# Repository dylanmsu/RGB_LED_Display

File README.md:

# RGB Led Display

## Board
| Front | Back |
|---|---|
| |  |

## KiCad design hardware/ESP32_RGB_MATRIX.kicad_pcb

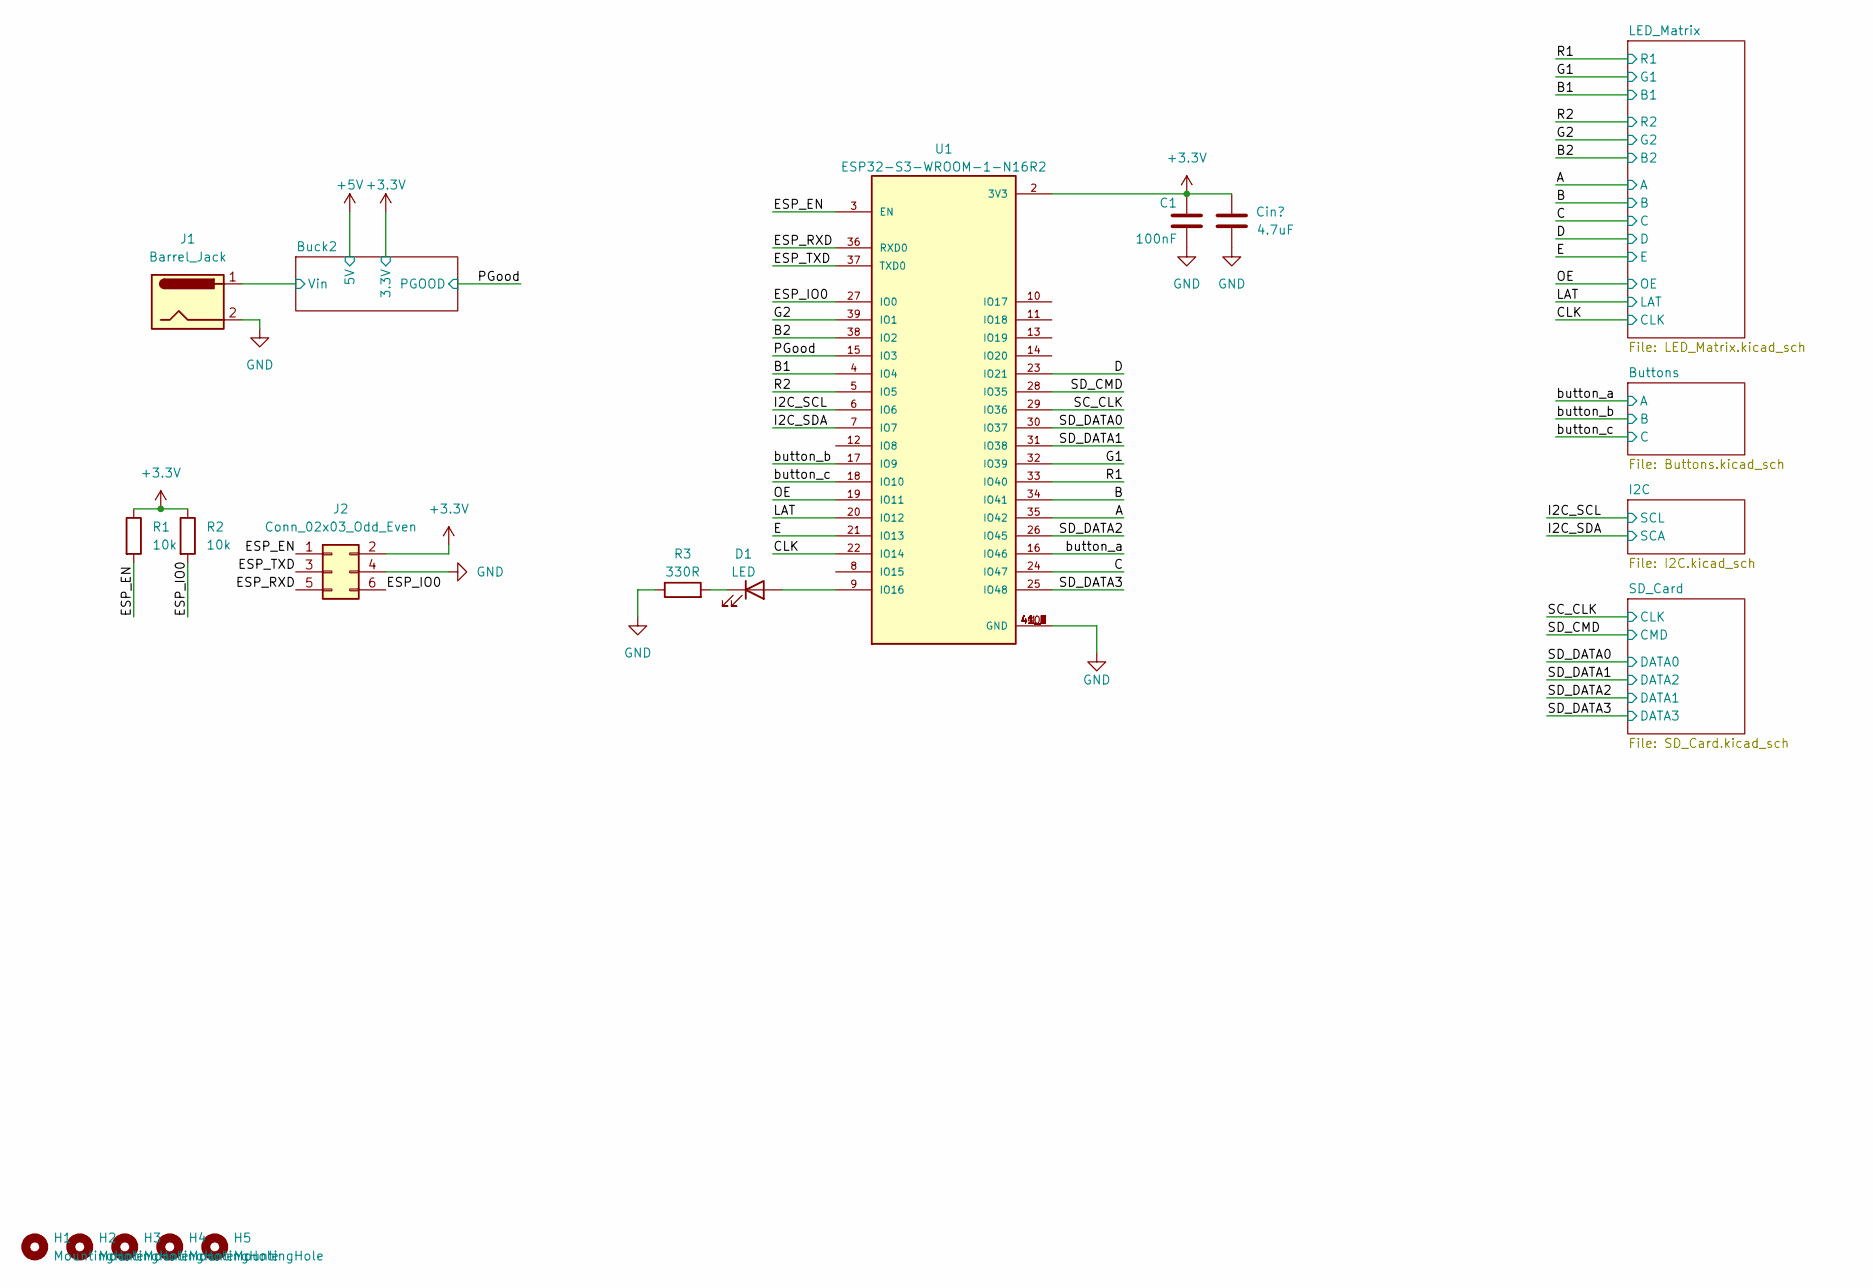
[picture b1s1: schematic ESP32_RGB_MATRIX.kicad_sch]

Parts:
C1: 100nF; C_0603_1608Metric
C2: 4.7uF; C_0805_2012Metric
D1: LED; LED_0805_2012Metric
H1, H2, H3, H4, H5: MountingHole; MountingHole_3.2mm_M3_DIN965_Pad
J1: Barrel_Jack; BarrelJack_Wuerth_6941xx301002
J2: Conn_02x03_Odd_Even; IDC-Header_2x03_P2.54mm_Vertical
R1, R2: 10k; R_0603_1608Metric
R3: 330R; R_0603_1608Metric
U1: ESP32-S3-WROOM-1-N16R2; XCVR_ESP32-S3-WROOM-1-N16R2; PARTREV v1.0

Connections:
+3.3V: C1.1, C2.1, J2.2, R1.1, R2.1, U1.2 (3V3); also elsewhere on the board
/A: U1.35 (IO42); also elsewhere on the board
/B: U1.34 (IO41); also elsewhere on the board
/B1: U1.4 (IO4); also elsewhere on the board
/B2: U1.38 (IO2); also elsewhere on the board
/Buck2/Vin: J1.1; also elsewhere on the board
/C: U1.24 (IO47); also elsewhere on the board
/CLK: U1.22 (IO14); also elsewhere on the board
/D: U1.23 (IO21); also elsewhere on the board
/E: U1.21 (IO13); also elsewhere on the board
/ESP_EN: J2.1, R1.2, U1.3 (EN)
/ESP_IO0: J2.6, R2.2, U1.27 (IO0)
/ESP_RXD: J2.5, U1.36 (RXD0)
/ESP_TXD: J2.3, U1.37 (TXD0)
/G1: U1.32 (IO39); also elsewhere on the board
/G2: U1.39 (IO1); also elsewhere on the board
/I2C_SCL: U1.6 (IO6); also elsewhere on the board
/I2C_SDA: U1.7 (IO7); also elsewhere on the board
/LAT: U1.20 (IO12); also elsewhere on the board
/OE: U1.19 (IO11); also elsewhere on the board
/PGood: U1.15 (IO3); also elsewhere on the board
/R1: U1.33 (IO40); also elsewhere on the board
/R2: U1.5 (IO5); also elsewhere on the board
/SC_CLK: U1.29 (IO36); also elsewhere on the board
/SD_CMD: U1.28 (IO35); also elsewhere on the board
/SD_DATA0: U1.30 (IO37); also elsewhere on the board
/SD_DATA1: U1.31 (IO38); also elsewhere on the board
/SD_DATA2: U1.26 (IO45); also elsewhere on the board
/SD_DATA3: U1.25 (IO48); also elsewhere on the board
/button_a: U1.16 (IO46); also elsewhere on the board
/button_b: U1.17 (IO9); also elsewhere on the board
/button_c: U1.18 (IO10); also elsewhere on the board
GND: C1.2, C2.2, J1.2, J2.4, R3.1, U1.1 (GND), U1.40 (GND), U1.41_1 (GND), U1.41_2 (GND), U1.41_3 (GND), U1.41_4 (GND), U1.41_5 (GND), U1.41_6 (GND), U1.41_7 (GND), U1.41_8 (GND), U1.41_9 (GND); also elsewhere on the board
unnamed: D1.2 (A), U1.9 (IO16)
unnamed: D1.1 (K), R3.2

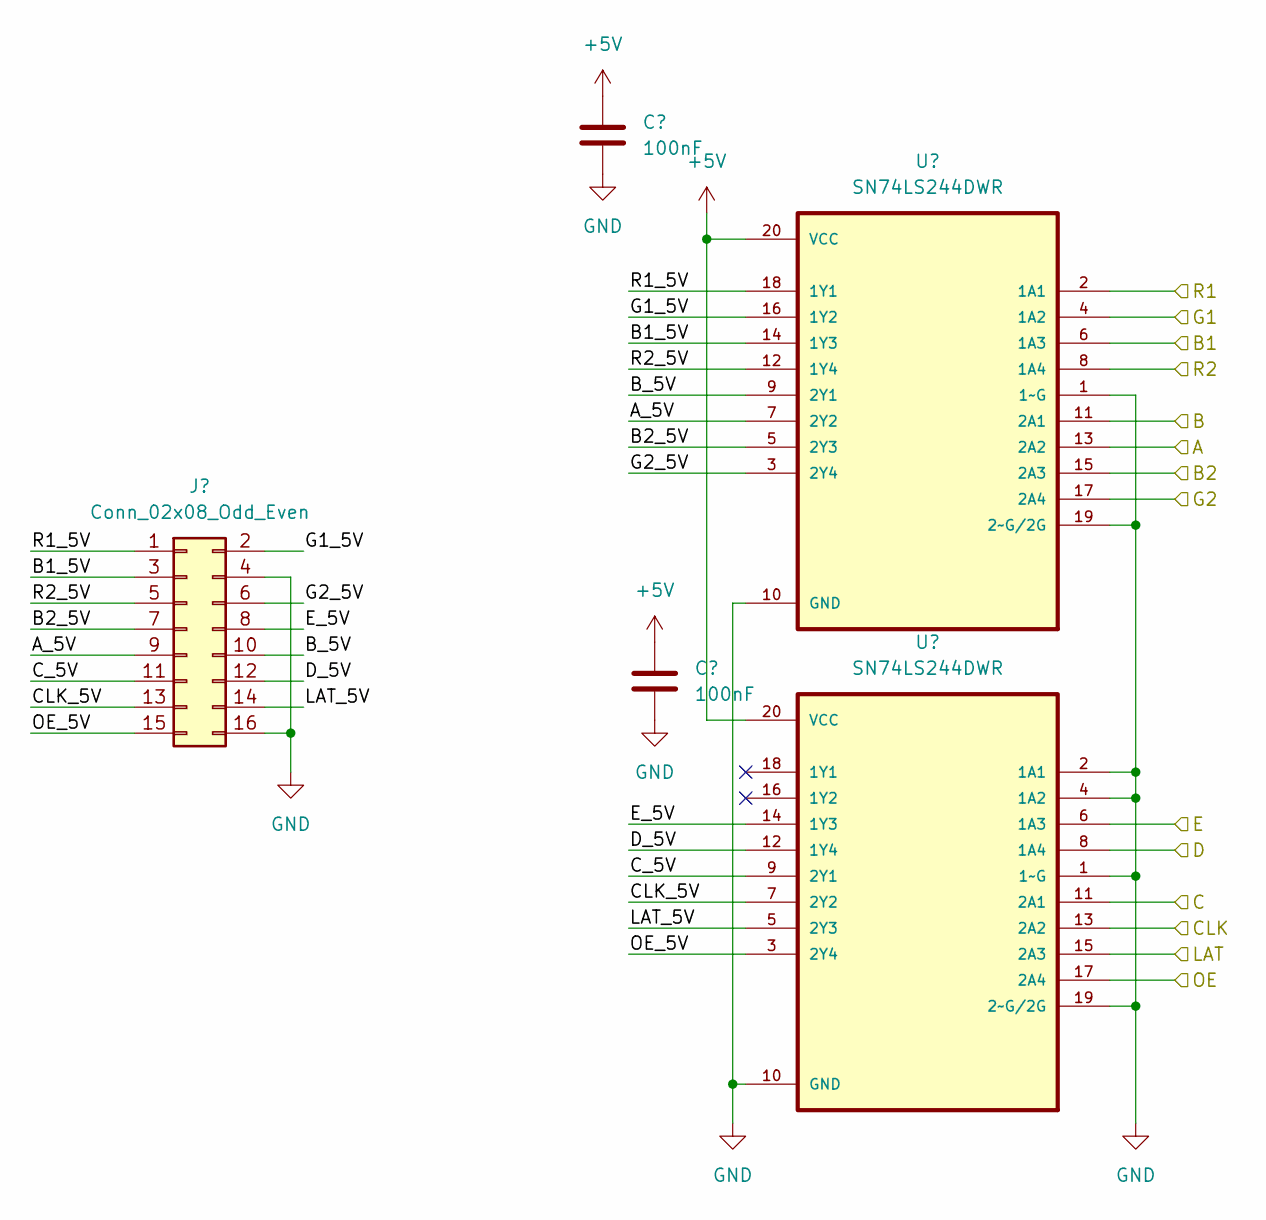
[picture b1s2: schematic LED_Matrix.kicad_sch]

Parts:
C10, C11: 100nF; C_0603_1608Metric
J6: Conn_02x08_Odd_Even; IDC-Header_2x08_P2.54mm_Vertical
U6, U7: SN74LS244DWR; SOIC-20W_7.5x12.8mm_P1.27mm

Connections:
+5V: C10.1, C11.1, U6.20 (VCC), U7.20 (VCC); also elsewhere on the board
/A: U6.13 (2A2); also elsewhere on the board
/B: U6.11 (2A1); also elsewhere on the board
/B1: U6.6 (1A3); also elsewhere on the board
/B2: U6.15 (2A3); also elsewhere on the board
/C: U7.11 (2A1); also elsewhere on the board
/CLK: U7.13 (2A2); also elsewhere on the board
/D: U7.8 (1A4); also elsewhere on the board
/E: U7.6 (1A3); also elsewhere on the board
/G1: U6.4 (1A2); also elsewhere on the board
/G2: U6.17 (2A4); also elsewhere on the board
/LAT: U7.15 (2A3); also elsewhere on the board
/LED_Matrix/A_5V: J6.9, U6.7 (2Y2)
/LED_Matrix/B1_5V: J6.3, U6.14 (1Y3)
/LED_Matrix/B2_5V: J6.7, U6.5 (2Y3)
/LED_Matrix/B_5V: J6.10, U6.9 (2Y1)
/LED_Matrix/CLK_5V: J6.13, U7.7 (2Y2)
/LED_Matrix/C_5V: J6.11, U7.9 (2Y1)
/LED_Matrix/D_5V: J6.12, U7.12 (1Y4)
/LED_Matrix/E_5V: J6.8, U7.14 (1Y3)
/LED_Matrix/G1_5V: J6.2, U6.16 (1Y2)
/LED_Matrix/G2_5V: J6.6, U6.3 (2Y4)
/LED_Matrix/LAT_5V: J6.14, U7.5 (2Y3)
/LED_Matrix/OE_5V: J6.15, U7.3 (2Y4)
/LED_Matrix/R1_5V: J6.1, U6.18 (1Y1)
/LED_Matrix/R2_5V: J6.5, U6.12 (1Y4)
/OE: U7.17 (2A4); also elsewhere on the board
/R1: U6.2 (1A1); also elsewhere on the board
/R2: U6.8 (1A4); also elsewhere on the board
GND: C10.2, C11.2, J6.4, J6.16, U6.1 (1~G), U6.10 (GND), U6.19 (2~G/2G), U7.1 (1~G), U7.2 (1A1), U7.4 (1A2), U7.10 (GND), U7.19 (2~G/2G); also elsewhere on the board

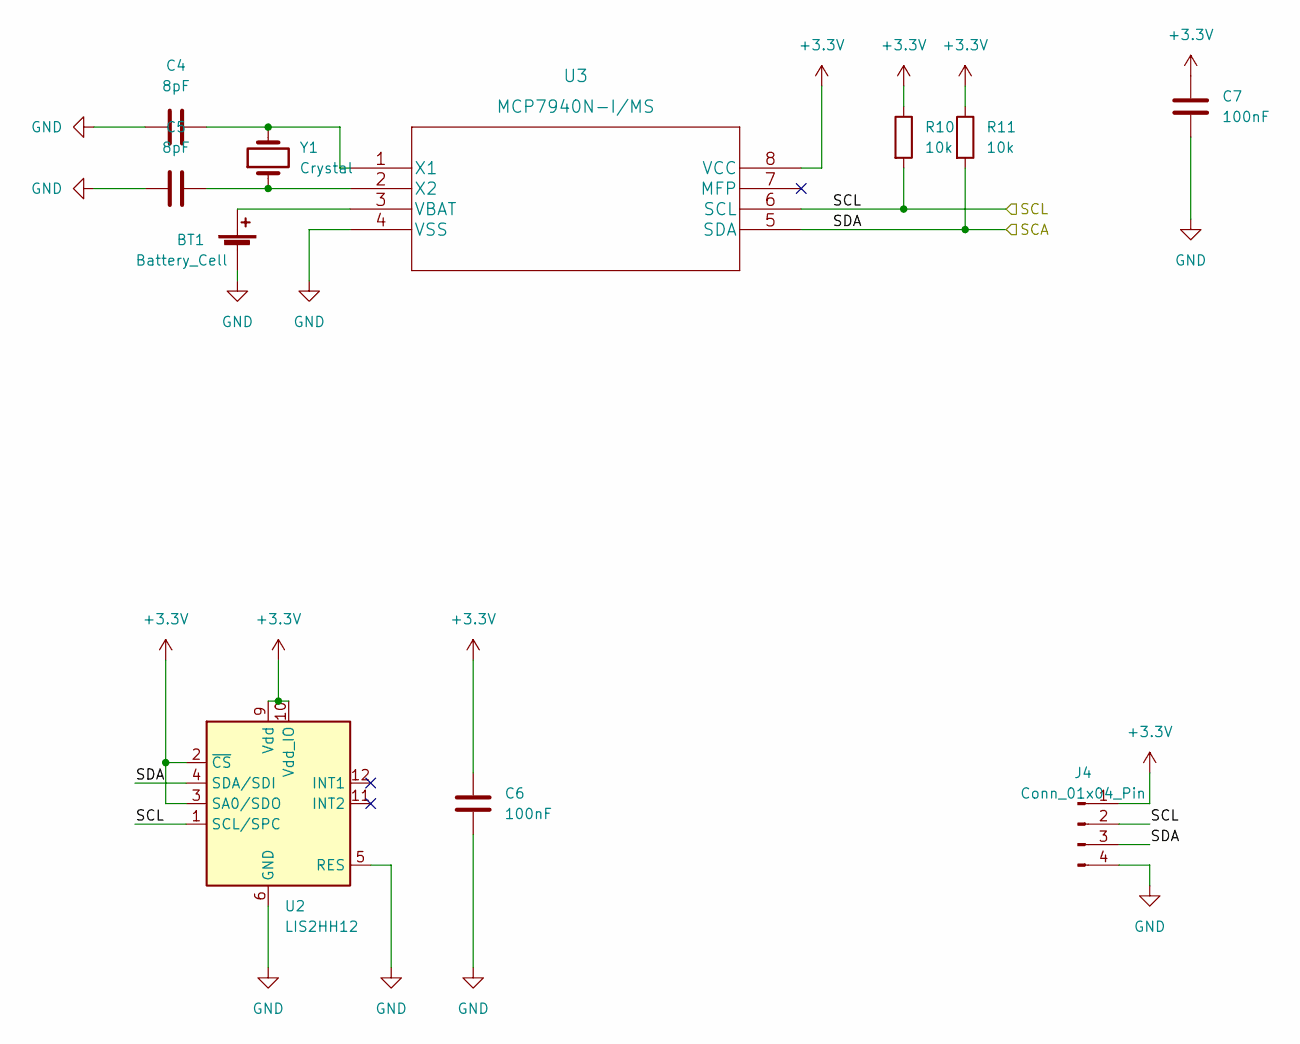
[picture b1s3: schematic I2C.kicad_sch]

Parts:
BT1: Battery_Cell; BatteryHolder_LINX_BAT-HLD-012-SMT
C4, C5: 8pF; C_0603_1608Metric
C6, C7: 100nF; C_0603_1608Metric
J4: Conn_01x04_Pin; PinSocket_1x04_P2.54mm_Vertical
R10, R11: 10k; R_0603_1608Metric
U2: LIS2HH12; LGA-12_2x2mm_P0.5mm
U3: MCP7940N-I/MS; MSOP-8-1EP_3x3mm_P0.65mm_EP1.68x1.88mm
Y1: Crystal; Crystal_SMD_2012-2Pin_2.0x1.2mm

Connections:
+3.3V: C6.1, C7.1, J4.1, R10.1, R11.1, U2.2 (~CS), U2.3 (SA0/SDO), U2.9 (Vdd), U2.10 (Vdd_IO), U3.8 (VCC); also elsewhere on the board
/I2C_SCL: J4.2, R10.2, U2.1 (SCL/SPC), U3.6 (SCL); also elsewhere on the board
/I2C_SDA: J4.3, R11.2, U2.4 (SDA/SDI), U3.5 (SDA); also elsewhere on the board
GND: BT1.2 (-), C4.1, C5.1, C6.2, C7.2, J4.4, U2.5 (RES), U2.6 (GND), U2.7 (GND), U2.8 (GND), U3.4 (VSS); also elsewhere on the board
unnamed: BT1.1 (+), U3.3 (VBAT)
unnamed: C4.2, U3.1 (X1), Y1.2
unnamed: C5.2, U3.2 (X2), Y1.1

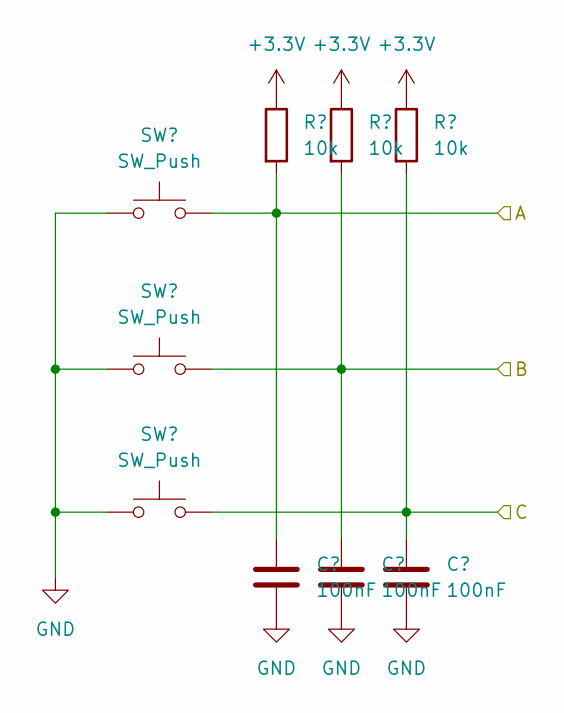
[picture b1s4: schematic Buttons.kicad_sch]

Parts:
C12, C13, C14: 100nF; C_0603_1608Metric
R14, R15, R16: 10k; R_0603_1608Metric
SW1, SW2, SW3: SW_Push; SW_PUSH_6mm

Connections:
+3.3V: R14.1, R15.1, R16.1; also elsewhere on the board
/button_a: C12.1, R14.2, SW1.2; also elsewhere on the board
/button_b: C13.1, R15.2, SW2.2; also elsewhere on the board
/button_c: C14.1, R16.2, SW3.2; also elsewhere on the board
GND: C12.2, C13.2, C14.2, SW1.1, SW2.1, SW3.1; also elsewhere on the board

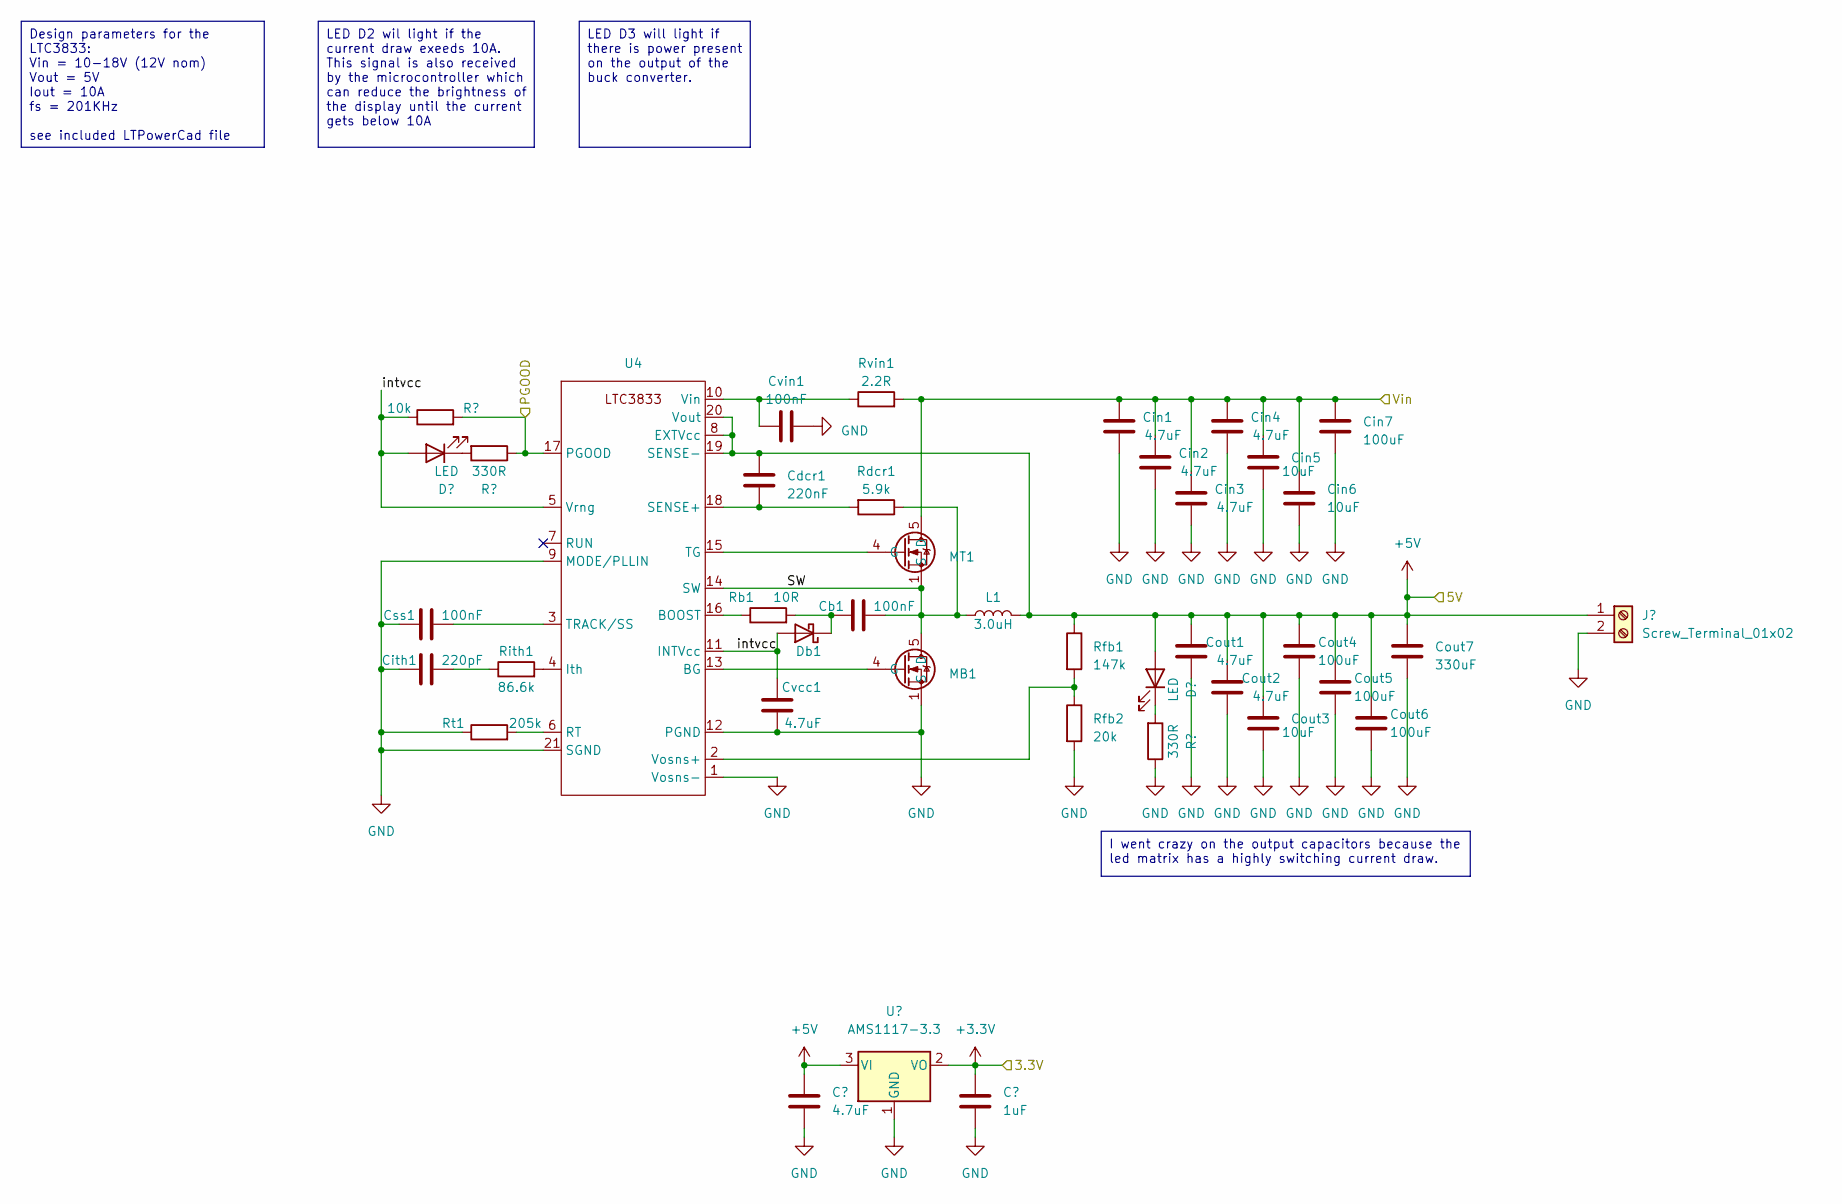
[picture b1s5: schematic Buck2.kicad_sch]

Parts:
C8: 4.7uF; C_0805_2012Metric
C9: 1uF; C_0805_2012Metric
Cb1: 100nF; C_0603_1608Metric
Cdcr1: 220nF; C_0603_1608Metric
Cin1, Cin2, Cin3, Cin4: 4.7uF; C_0805_2012Metric
Cin5, Cin6: 10uF; C_1206_3216Metric
Cin7: 100uF; C_Elec_8x5.4
Cith1: 220pF; C_0603_1608Metric
Cout1, Cout2: 4.7uF; C_0805_2012Metric
Cout3: 10uF; C_1206_3216Metric
Cout4, Cout5, Cout6: 100uF; C_Elec_8x5.4
Cout7: 330uF; CP_EIA-7343-15_Kemet-W
Css1: 100nF; C_0603_1608Metric
Cvcc1: 4.7uF; C_0805_2012Metric
Cvin1: 100nF; C_0603_1608Metric
D2, D3: LED; LED_0805_2012Metric
Db1: D_Schottky; D_SOD-323
J5: Screw_Terminal_01x02; TerminalBlock_Dinkle_DT-55-B01X-02_P10.00mm
L1: 3.0uH; IHLP-5050EZ-5A
MB1: Infineon_PG-TDSON-8_6.15x5.15mm
MT1: Infineon_PG-TDSON-8_6.15x5.15mm
R12, R13: 330R; R_0603_1608Metric
Rb1: 10R; R_0603_1608Metric
Rdcr1: 5.9k; R_0603_1608Metric
Rfb1: 147k; R_0603_1608Metric
Rfb2: 20k; R_0603_1608Metric
Rith1: 86.6k; R_0603_1608Metric
Rpg1: 10k; R_0603_1608Metric
Rt1: 205k; R_0603_1608Metric
Rvin1: 2.2R; R_0603_1608Metric
U4: QFN-20-1EP_3x4mm_P0.5mm_EP1.65x2.65mm_ThermalVias
U5: AMS1117-3.3; SOT-223-3_TabPin2

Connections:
+3.3V: C9.1, U5.2 (VO); also elsewhere on the board
+5V: C8.1, Cdcr1.2, Cout1.1, Cout2.1, Cout3.1, Cout4.1, Cout5.1, Cout6.1, Cout7.1, D3.2 (A), J5.1, L1.2, Rfb1.1, U4.8 (EXTVcc), U4.19 (SENSE-), U4.20 (Vout), U5.3 (VI); also elsewhere on the board
/Buck2/SW: Cb1.2, L1.1, MB1.5 (D), MT1.1 (S), MT1.2 (S), MT1.3 (S), Rdcr1.1, U4.14 (SW)
/Buck2/Vin: Cin1.1, Cin2.1, Cin3.1, Cin4.1, Cin5.1, Cin6.1, Cin7.1, MT1.5 (D), Rvin1.2; also elsewhere on the board
/Buck2/intvcc: Cvcc1.1, D2.2 (A), Db1.2 (A), Rpg1.1, U4.5 (Vrng), U4.11 (INTVcc)
/PGood: R12.1, Rpg1.2, U4.17 (PGOOD); also elsewhere on the board
GND: C8.2, C9.2, Cin1.2, Cin2.2, Cin3.2, Cin4.2, Cin5.2, Cin6.2, Cin7.2, Cith1.1, Cout1.2, Cout2.2, Cout3.2, Cout4.2, Cout5.2, Cout6.2, Cout7.2, Css1.2, Cvcc1.2, Cvin1.2, J5.2, MB1.1 (S), MB1.2 (S), MB1.3 (S), R13.1, Rfb2.2, Rt1.1, U4.1 (Vosns-), U4.9 (MODE/PLLIN), U4.12 (PGND), U4.21 (SGND), U5.1 (GND); also elsewhere on the board
unnamed: Cith1.2, Rith1.1
unnamed: D2.1 (K), R12.2
unnamed: D3.1 (K), R13.2
unnamed: Cb1.1, Db1.1 (K), Rb1.2
unnamed: MB1.4 (G), U4.13 (BG)
unnamed: MT1.4 (G), U4.15 (TG)
unnamed: Rb1.1, U4.16 (BOOST)
unnamed: Rith1.2, U4.4 (Ith)
unnamed: Rt1.2, U4.6 (RT)
unnamed: Cdcr1.1, Rdcr1.2, U4.18 (SENSE+)
unnamed: Css1.1, U4.3 (TRACK/SS)
unnamed: Cvin1.1, Rvin1.1, U4.10 (Vin)
unnamed: Rfb1.2, Rfb2.1, U4.2 (Vosns+)

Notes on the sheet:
I went crazy on the output capacitors because the led matrix has a highly switching current draw.
LED D2 wil light if the current draw exeeds 10A. This signal is also received by the microcontroller which can reduce the brightness of the display until the current gets below 10A
Design parameters for the LTC3833: Vin = 10-18V (12V nom) Vout = 5V Iout = 10A fs = 201KHz see included LTPowerCad file
LED D3 will light if there is power present on the output of the buck converter.

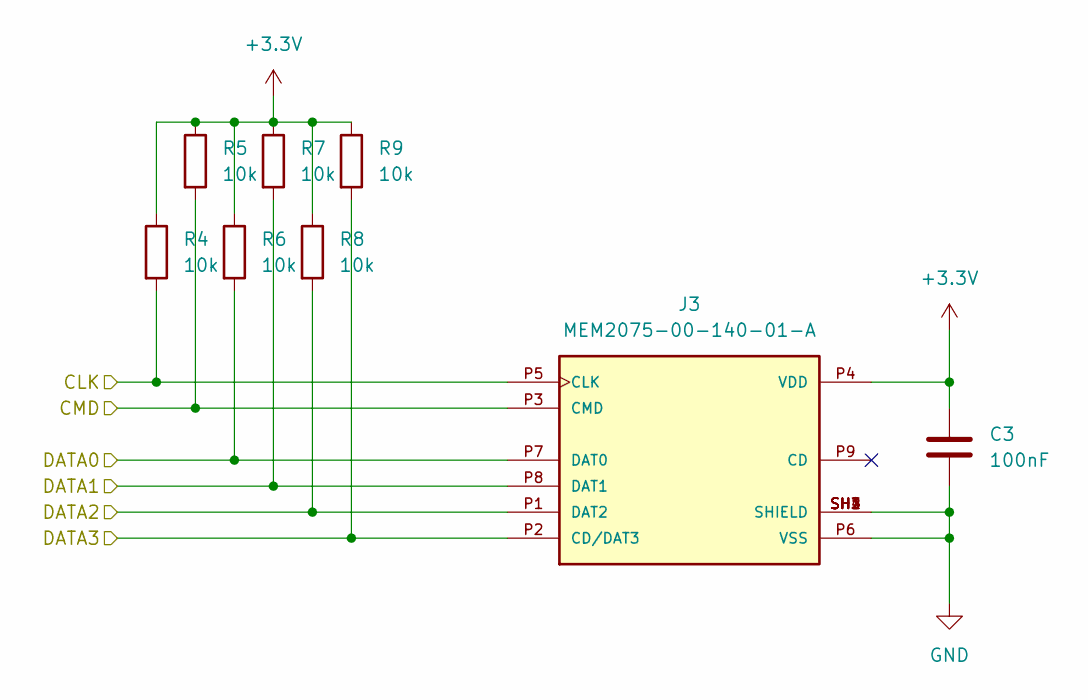
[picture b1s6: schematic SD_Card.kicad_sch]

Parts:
C3: 100nF; C_0603_1608Metric
J3: MEM2075-00-140-01-A; GCT_MEM2075-00-140-01-A; PARTREV A
R4, R5, R6, R7, R8, R9: 10k; R_0603_1608Metric

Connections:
+3.3V: C3.1, J3.P4 (VDD), R4.1, R5.1, R6.1, R7.1, R8.1, R9.1; also elsewhere on the board
/SC_CLK: J3.P5 (CLK), R4.2; also elsewhere on the board
/SD_CMD: J3.P3 (CMD), R5.2; also elsewhere on the board
/SD_DATA0: J3.P7 (DAT0), R6.2; also elsewhere on the board
/SD_DATA1: J3.P1 (DAT2), R8.2; also elsewhere on the board
/SD_DATA2: J3.P8 (DAT1), R7.2; also elsewhere on the board
/SD_DATA3: J3.P2 (CD/DAT3), R9.2; also elsewhere on the board
GND: C3.2, J3.P6 (VSS), J3.SH1 (SHIELD), J3.SH2 (SHIELD), J3.SH3 (SHIELD), J3.SH4 (SHIELD); also elsewhere on the board

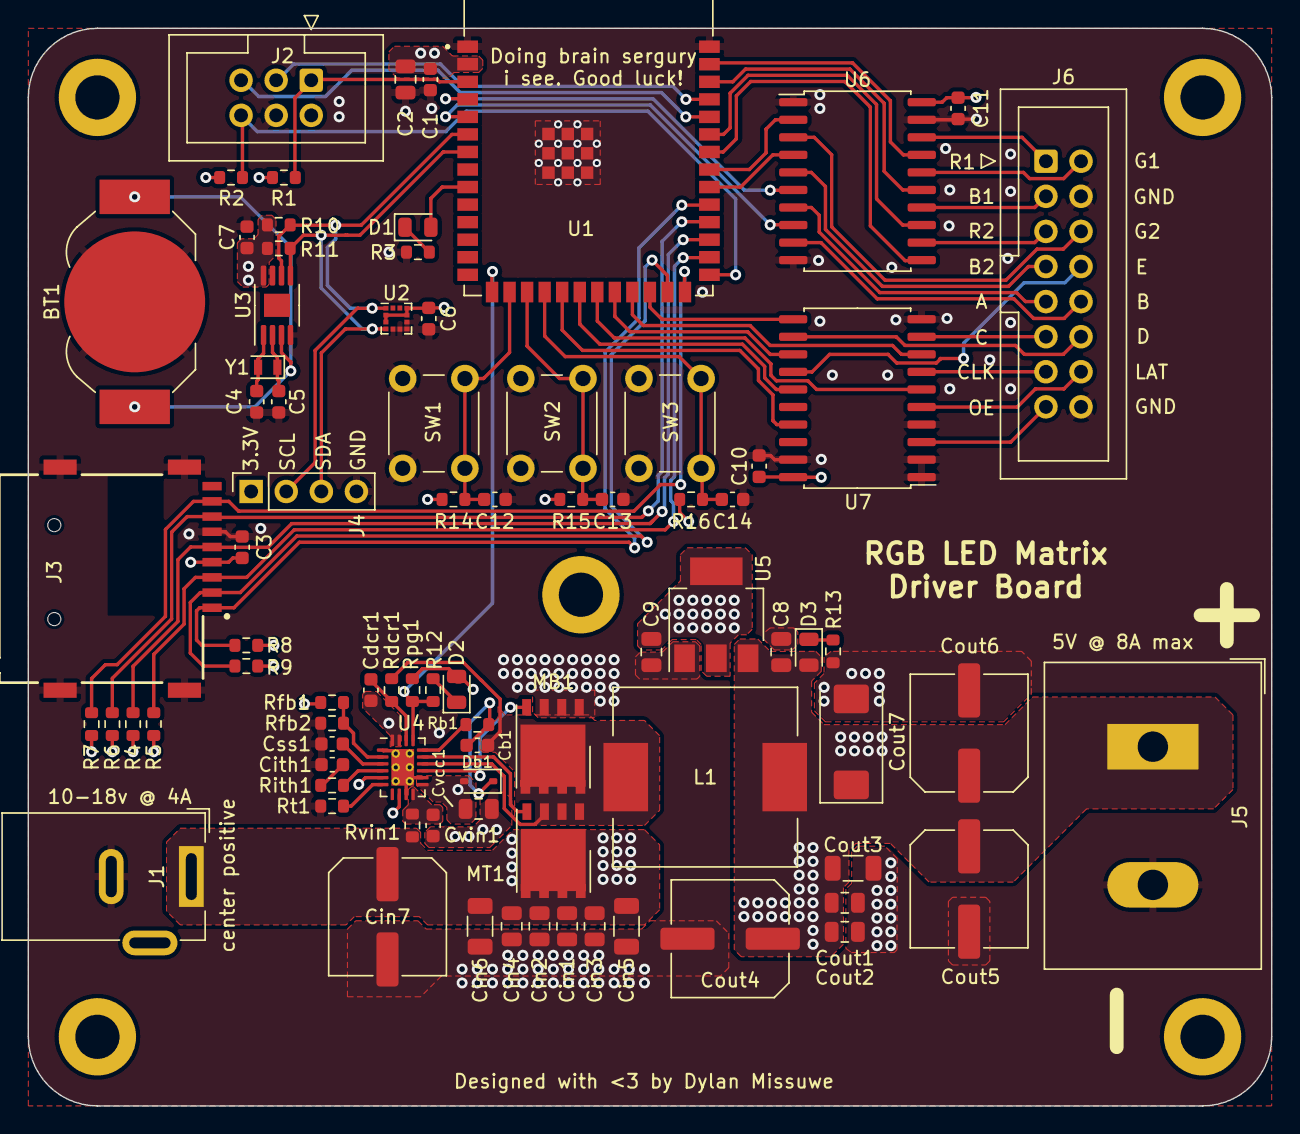
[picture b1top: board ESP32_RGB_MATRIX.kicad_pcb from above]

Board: 4 copper layers, 90.0 x 78.0 mm, 88 parts (0 on the bottom side), 68 nets.

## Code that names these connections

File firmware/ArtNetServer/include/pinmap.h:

#define V2

#ifdef V1

    // HUB75 connections
    #define R1_PIN          25
    #define G1_PIN          26
    #define B1_PIN          27
    #define R2_PIN          15
    #define G2_PIN          7
    #define B2_PIN          2

    #define A_PIN           32
    #define B_PIN           33
    #define C_PIN           5
    #define D_PIN           -1
    #define E_PIN           -1

    #define LAT_PIN         4
    #define OE_PIN          19
    #define CLK_PIN         8

    // SD_Card
    #define PIN_NUM_MISO    12
    #define PIN_NUM_MOSI    13
    #define PIN_NUM_CLK     14
    #define PIN_NUM_CS      20

    #define SD_CMD          PIN_NUM_MOSI
    #define SD_CLK          PIN_NUM_CLK
    #define SD_DATA0        PIN_NUM_MISO
    #define SD_DATA1        -1
    #define SD_DATA2        -1
    #define SD_DATA3        PIN_NUM_CS

    // I2C
    #define PIN_I2C_SDA     21
    #define PIN_I2C_SCL     22

    // Buttons
    #define BUTTON_A        39
    #define BUTTON_B        38
    #define BUTTON_C        37

#endif

#ifdef V2

    // HUB75 connections
    #define R1_PIN          40
    #define G1_PIN          39
    #define B1_PIN          4
    #define R2_PIN          5
    #define G2_PIN          1
    #define B2_PIN          2

    #define A_PIN           42
    #define B_PIN           41
    #define C_PIN           47
    #define D_PIN           21
    #define E_PIN           13

    #define LAT_PIN         12
    #define OE_PIN          11
    #define CLK_PIN         14

    // SD_Card
    #define PIN_NUM_MISO    37
    #define PIN_NUM_MOSI    35
    #define PIN_NUM_CLK     36
    #define PIN_NUM_CS      48

    #define SD_CMD          35
    #define SD_CLK          36
    #define SD_DATA0        37
    #define SD_DATA1        38
    #define SD_DATA2        45
    #define SD_DATA3        48

    // I2C
    #define PIN_I2C_SDA     7
    #define PIN_I2C_SCL     6

    // Buttons
    #define BUTTON_A        46
    #define BUTTON_B        9
    #define BUTTON_C        10

    // Other
    #define P_GOOD          3

#endif

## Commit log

2023-02-06 made 3d engine more oo and added more lua scripts
2023-02-19 restructured lua api and libraries
2023-02-19 added lua script scanner
2023-02-27 fixed memory issue on the 3d library
2023-02-28 refactored and implemented time keeping
2023-03-02 implemented Xiaomlin Wu line drawing algorithm
2023-03-02 improved thread safety
2023-03-02 implemented a double buffer and transparency
2023-03-02 improved transparency
2023-03-14 speed improvements
2023-03-14 fix linking error
2023-03-15 implemented basic box2d functionality
2023-03-15 implemented normal precalculation for potential speed improvement
2023-03-15 update 3d lua script
2023-03-15 finetuned box2d library and added lua example
2023-03-15 implemented wireframe drawing in the 3d library
2023-03-20 Create LICENCE
2023-03-29 added support for new hardware
2023-03-30 update 3d library and lua api
2023-04-10 implemented art-net protocol
2023-04-28 restructured repository and included hardware design files
2023-05-01 separated script sandbox and artnet server into two pio projects
